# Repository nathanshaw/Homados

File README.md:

# Homados

16 Channel Solenoid Driver

Please note that for each board you much change the ARDUINO_ID to a unique number

If you want to turn off LED feedback change LED_FEEDBACK to 0

If you don't want the startup sequence change BOOT_TEST to 0

If the LED is not yellow during the BOOT_TEST change your led pins until it is.

-------------------

Homados is the larger of the two actuator shields in the Pantheon system and is 
fashioned for use with the Arduino Mega microcontroller. The board supports 
sixteen channels of actuator control, three I2C jacks, and a RGB status LED. The 
first fifteen channels of the Homados driver utilizes PWM while the sixteenth channel 
uses a standard digital pin. The Homados is intended to function as a larger version of 
the Brigid shield and is to be used when six channels of control are inadequate. The 
Homados shield is functionally comparable to the Brigid in all ways.

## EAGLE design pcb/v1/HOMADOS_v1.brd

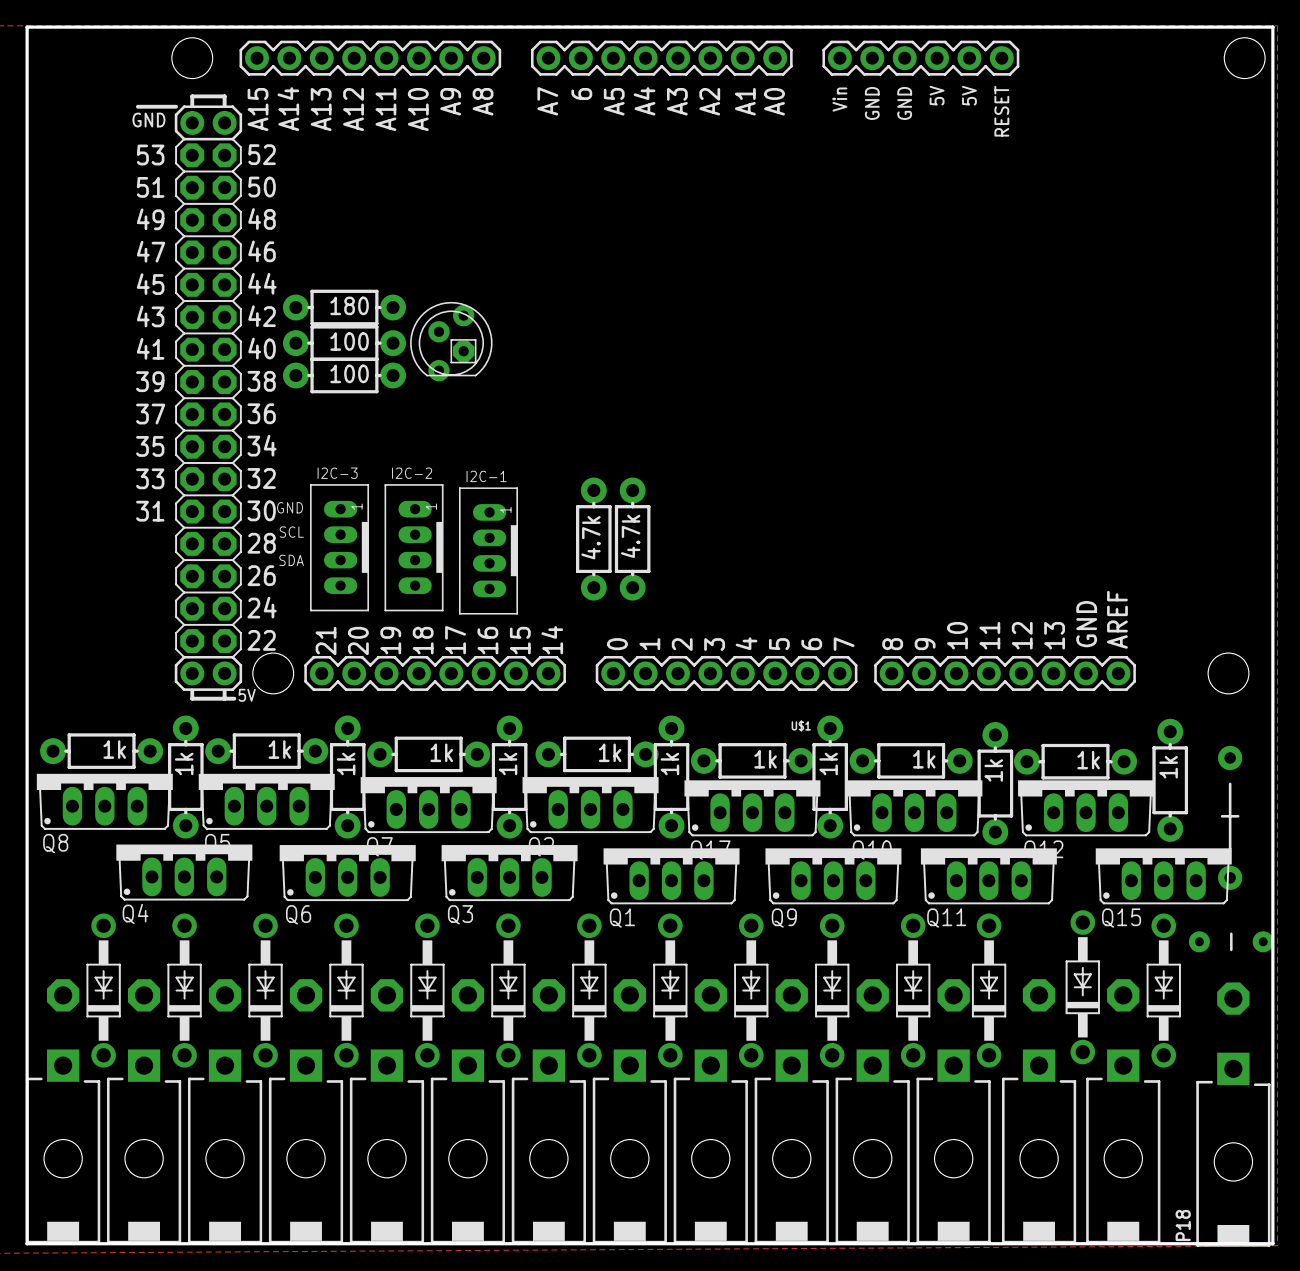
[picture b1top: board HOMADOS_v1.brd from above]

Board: 2 copper layers, 97.7 x 95.4 mm, 69 parts (0 on the bottom side), 54 nets, no tracks yet.

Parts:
C1: CAP-PTH-5MM
C2: CAP-PTH-LARGE
D1, D2, D3, D4, D5, D6, D7, D8, D9, D10, D11, D12, D13, D16: 1N4004; DO41-10
I2C-1, I2C-2, I2C-3: JST-PH_4-PIN_HEADER; JST_B4B-PH_HEADER
P1, P3, P4, P5, P6, P7, P8, P9, P10, P11, P12, P13, P14, P17, P18: 39-30-02?; 39-30-?02?
Q1, Q2, Q3, Q4, Q5, Q6, Q7, Q8, Q9, Q10, Q11, Q12, Q15, Q17: TO220BV
R1, R2: 4.7k; AXIAL-0.3-KIT
R3: 180; AXIAL-0.3-KIT
R4, R5, R6, R7, R8, R9, R10, R11, R12, R13, R14, R15, R18, R19: 1k; AXIAL-0.3-KIT
R20, R21: 100; AXIAL-0.3-KIT
U$1: ARDUINO_MEGA
U$2: RGBLED_CA; LED5MMRGB

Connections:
5V: I2C-1.P4, I2C-2.P4, I2C-3.P4, R1.P$2, R2.P$1, U$1.5V@1, U$1.5V@2
A0: R3.P$1, U$2.4
A2: R20.P$1, U$2.1
ARDUINO_GND: U$1.GND@2, U$2.2
BLUE: R3.P$2, U$1.42
D0: R15.P$1, U$1.47
GND: C1.2, C2.2, I2C-1.P1, I2C-2.P1, I2C-3.P1, P18.2, Q1.S, Q2.S, Q3.S, Q4.S, Q5.S, Q6.S, Q7.S, Q8.S, Q9.S, Q10.S, Q11.S, Q12.S, Q15.S, Q17.S, U$1.GND@3, U$1.GND@4
GREEN: R21.P$2, U$1.40
unnamed: R21.P$1, U$2.3
unnamed: D2.A, P3.2, Q17.D
unnamed: D5.A, P6.2, Q7.D
unnamed: D12.A, P13.2, Q11.D
unnamed: Q17.G, R19.P$2
unnamed: Q1.G, R4.P$2
unnamed: D13.A, P14.2, Q15.D
unnamed: Q2.G, R5.P$2
unnamed: D1.A, P1.2, Q1.D
unnamed: D3.A, P4.2, Q2.D
unnamed: Q3.G, R6.P$2
unnamed: D4.A, P5.2, Q3.D
unnamed: D6.A, P7.2, Q6.D
unnamed: D7.A, P8.2, Q5.D
unnamed: Q7.G, R7.P$2
unnamed: D11.A, P12.2, Q10.D
unnamed: Q6.G, R8.P$2
unnamed: D8.A, P9.2, Q4.D
unnamed: Q5.G, R9.P$2
unnamed: D16.A, P17.2, Q12.D
unnamed: D10.A, P11.2, Q9.D
unnamed: Q4.G, R10.P$2
unnamed: D9.A, P10.2, Q8.D
unnamed: Q8.G, R11.P$2
unnamed: Q9.G, R12.P$2
unnamed: Q10.G, R13.P$2
unnamed: Q11.G, R14.P$2
unnamed: Q15.G, R15.P$2
unnamed: Q12.G, R18.P$2
PW0: R14.P$1, U$1.2
PW1: R13.P$1, U$1.3
PW2: R12.P$1, U$1.4
PW3: R19.P$1, U$1.5
PW4: R4.P$1, U$1.6
PW5: R5.P$1, U$1.7
PW6: R6.P$1, U$1.8
PW7: R7.P$1, U$1.9
PW8: R8.P$1, U$1.10
PW9: R11.P$1, U$1.11
PW10: R10.P$1, U$1.12
PW11: R9.P$1, U$1.13
PW12: R18.P$1, U$1.44
PWR: C1.1, C2.1, D1.C, D2.C, D3.C, D4.C, D5.C, D6.C, D7.C, D8.C, D9.C, D10.C, D11.C, D12.C, D13.C, D16.C, P1.1, P3.1, P4.1, P5.1, P6.1, P7.1, P8.1, P9.1, P10.1, P11.1, P12.1, P13.1, P14.1, P17.1, P18.1
RED: R20.P$2, U$1.41
SCL: I2C-1.P2, I2C-2.P2, I2C-3.P2, R2.P$2, U$1.21
SDA: I2C-1.P3, I2C-2.P3, I2C-3.P3, R1.P$1, U$1.20

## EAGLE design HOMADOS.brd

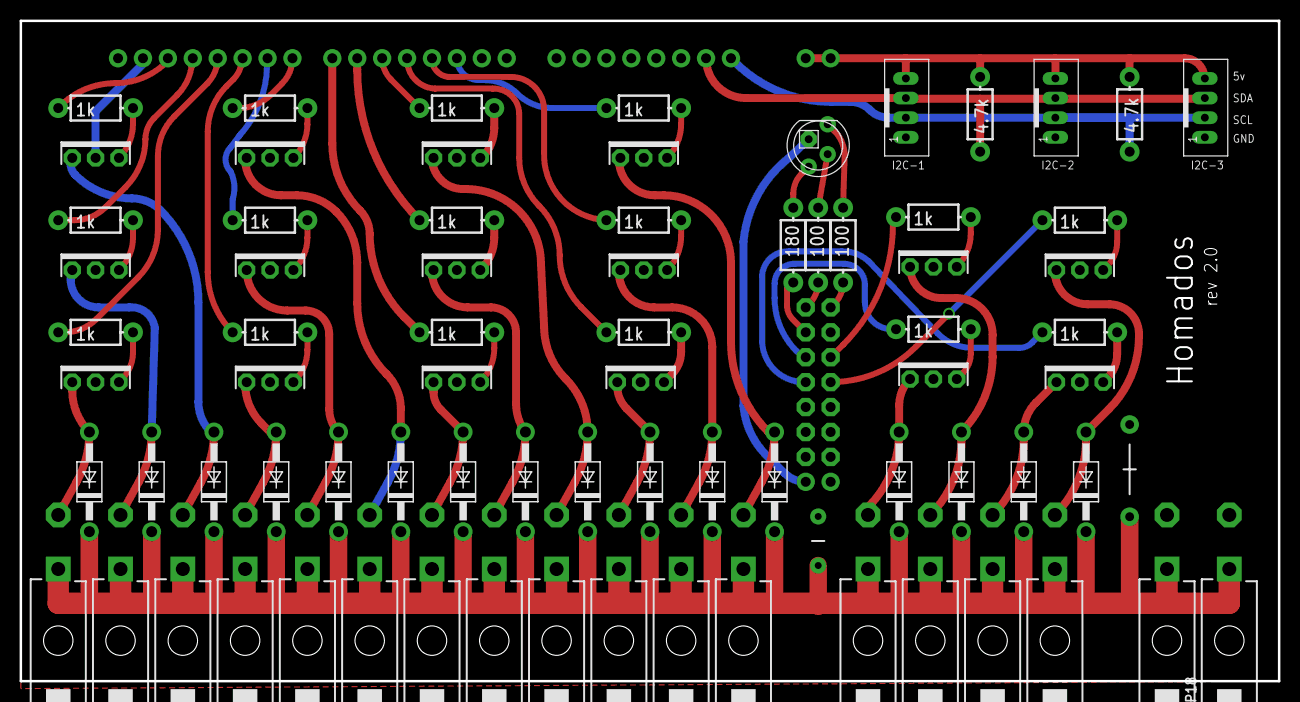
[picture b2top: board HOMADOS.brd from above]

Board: 2 copper layers, 128.3 x 67.3 mm, 78 parts (0 on the bottom side), 60 nets.

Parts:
C1: CAP-PTH-5MM
C2: CAP-PTH-LARGE
D1, D2, D3, D4, D5, D6, D7, D8, D9, D10, D11, D12, D13, D14, D15, D16: 1N4004; DO41-10
I2C-1, I2C-2, I2C-3: JST-PH_4-PIN_HEADER; JST_B4B-PH_HEADER
P1, P2, P3, P4, P5, P6, P7, P8, P9, P10, P11, P12, P13, P14, P15, P16, P17, P18: 39-30-02?; 39-30-?02?
Q1, Q2, Q3, Q4, Q5, Q6, Q7, Q8, Q9, Q10, Q11, Q12, Q13, Q14, Q15, Q16: T460; TO225AAV
R1, R2: 4.7k; AXIAL-0.3-KIT
R3: 180; AXIAL-0.3-KIT
R4, R5, R6, R7, R8, R9, R10, R11, R12, R13, R14, R15, R16, R17, R18, R19: 1k; AXIAL-0.3-KIT
R20, R21: 100; AXIAL-0.3-KIT
U2: ARDUINO-MEGAPRO-5V; ARDUINO_MEGA-PRO-5V
U$2: RGBLED_CA; LED5MMRGB

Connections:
5V: I2C-1.P4, I2C-2.P4, I2C-3.P4, R1.P$2, R2.P$1, U2.5V@1, U2.5V@2
A0: R3.P$1, U$2.4
A2: R20.P$1, U$2.1
ARDUINO_GND: U2.GND@2, U$2.2
BLUE: R3.P$2, U2.42
D0: R15.P$1, U2.47
GND: C1.2, C2.2, I2C-1.P1, I2C-2.P1, I2C-3.P1, P2.2, P18.2, Q1.2, Q2.2, Q3.2, Q4.2, Q5.2, Q6.2, Q7.2, Q8.2, Q9.2, Q10.2, Q11.2, Q12.2, Q13.2, Q14.2, Q15.2, Q16.2, U2.GND@3, U2.GND@4
GREEN: R21.P$2, U2.22
unnamed: R21.P$1, U$2.3
unnamed: D2.A, P3.2, Q1.1
unnamed: D1.A, P1.2, Q2.1
unnamed: Q1.3, R19.P$2
unnamed: Q2.3, R4.P$2
unnamed: D3.A, P4.2, Q3.1
unnamed: Q3.3, R5.P$2
unnamed: D4.A, P5.2, Q4.1
unnamed: Q4.3, R6.P$2
unnamed: D5.A, P6.2, Q8.1
unnamed: Q8.3, R7.P$2
unnamed: D6.A, P7.2, Q7.1
unnamed: Q7.3, R8.P$2
unnamed: D7.A, P8.2, Q6.1
unnamed: Q6.3, R9.P$2
unnamed: D8.A, P9.2, Q5.1
unnamed: Q5.3, R10.P$2
unnamed: D9.A, P10.2, Q12.1
unnamed: Q12.3, R11.P$2
unnamed: D10.A, P11.2, Q11.1
unnamed: Q11.3, R12.P$2
unnamed: D11.A, P12.2, Q10.1
unnamed: Q10.3, R13.P$2
unnamed: D12.A, P13.2, Q9.1
unnamed: Q9.3, R14.P$2
unnamed: D13.A, P14.2, Q16.1
unnamed: Q16.3, R15.P$2
unnamed: D14.A, P15.2, Q15.1
unnamed: Q15.3, R16.P$2
unnamed: D15.A, P16.2, Q14.1
unnamed: Q14.3, R17.P$2
unnamed: D16.A, P17.2, Q13.1
unnamed: Q13.3, R18.P$2
PW0: R14.P$1, U2.2
PW1: R13.P$1, U2.3
PW2: R12.P$1, U2.4
PW3: R19.P$1, U2.5
PW4: R4.P$1, U2.6
PW5: R5.P$1, U2.7
PW6: R6.P$1, U2.8
PW7: R7.P$1, U2.9
PW8: R8.P$1, U2.10
PW9: R11.P$1, U2.11
PW10: R10.P$1, U2.12
PW11: R9.P$1, U2.13
PW12: R18.P$1, U2.44
PW13: R17.P$1, U2.45
PW14: R16.P$1, U2.46
PWR: C1.1, C2.1, D1.C, D2.C, D3.C, D4.C, D5.C, D6.C, D7.C, D8.C, D9.C, D10.C, D11.C, D12.C, D13.C, D14.C, D15.C, D16.C, P1.1, P2.1, P3.1, P4.1, P5.1, P6.1, P7.1, P8.1, P9.1, P10.1, P11.1, P12.1, P13.1, P14.1, P15.1, P16.1, P17.1, P18.1
RED: R20.P$2, U2.23
SCL: I2C-1.P2, I2C-2.P2, I2C-3.P2, R2.P$2, U2.21
SDA: I2C-1.P3, I2C-2.P3, I2C-3.P3, R1.P$1, U2.20

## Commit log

2016-12-13 created v2 of Homados board
2017-02-01 touch up on v2 board
2017-02-06 moved some things around
2017-02-07 added firmware to repo
2017-02-17 finished revision of homados
2017-03-16 updated Homados board and firmware
2017-06-07 added some specialized firmware
2017-06-08 added picture to readme, and made a legacy folder to hold specialized and old versions of the firmware.
2019-01-14 renamed the firmware files to be easier to understand
2021-05-25 Started to update the EAGLE design for production

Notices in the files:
parts and their libraries:
con-molex-mini-fit: Copyright (C) 2011, Bob Starr
SparkFun-Passives: Licensing: Creative Commons ShareAlike 4.0 International - https://creativecommons.org/licenses/by-sa/4.0
